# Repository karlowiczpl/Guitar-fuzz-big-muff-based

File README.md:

# Simple guitar fuzz based big muff

The Big Muff is a legendary guitar effects pedal known for its iconic fuzz tone. Its construction typically includes three stages: input buffer, clipping circuit, and output buffer. The input buffer maintains signal integrity, the clipping circuit generates the characteristic distortion, and the output buffer ensures signal strength. Its distinctive sound is cherished by guitarists worldwide

# Schematic

# 3d model

# files

### BRD:
[footprint.brd](footprint.brd)
### STL:
[model.stl](model.stl)
### SCH:
[schematic.sch](schematic.sch)

# Sample photos

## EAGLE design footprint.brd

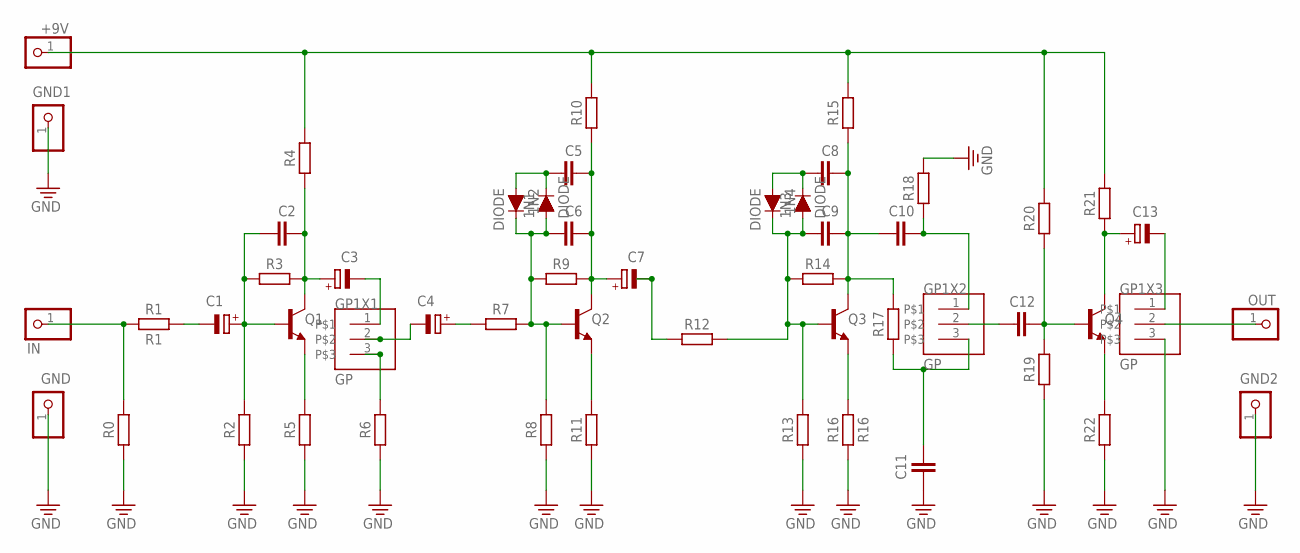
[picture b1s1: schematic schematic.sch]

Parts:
1N1, 1N2, 1N3, 1N4: DIODE; DIODE-1N4148
+9V: PINHD-1X1; 1X01
C1, C3, C4, C7, C13: C; CAP
C2, C5, C6, C8, C9, C10, C11, C12: CUN; CAPPRR250W50L310T100H650B
GND, GND1, GND2: PINHD-1X1; 1X01
GP1X1, GP1X2, GP1X3: GP; HDRV3W64P254_1X3_762X254X838B
IN: PINHD-1X1; 1X01
OUT: PINHD-1X1; 1X01
Q1, Q2, Q3, Q4: BC550B; TO92-EBC
R0, R2, R3, R4, R5, R6, R7, R8, R9, R10, R11, R12, R13, R14, R15, R17, R18, R19, R20, R21, R22: R_AXIAL-7.2MM-PITCH; RESAD724W46L381D178B
R1: R1; RESAD724W46L381D178B
R16: R16; RESAD724W46L381D178B

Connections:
GND: C11.1, GND.1, GND1.1, GND2.1, GP1X3.3, R0.1, R2.1, R5.1, R6.1, R8.1, R11.1, R13.1, R16.1, R18.2, R19.1, R22.1
unnamed: IN.1, R0.2, R1.1
unnamed: C1.2 (-), R1.2
unnamed: C1.1 (+), C2.1, Q1.B, R2.2, R3.1
unnamed: Q1.E, R5.2
unnamed: C2.2, C3.1 (+), Q1.C, R3.2, R4.1
unnamed: C3.2 (-), GP1X1.1
unnamed: C4.2 (-), GP1X1.2
unnamed: GP1X1.3, R6.2
unnamed: C4.1 (+), R7.1
unnamed: 1N1.A, 1N2.C, C6.1, Q2.B, R7.2, R8.2, R9.1
unnamed: C5.2, C6.2, C7.1 (+), Q2.C, R9.2, R10.1
unnamed: 1N1.C, 1N2.A, C5.1
unnamed: Q2.E, R11.2
unnamed: C7.2 (-), R12.1
unnamed: 1N3.A, 1N4.C, C9.1, Q3.B, R12.2, R13.2, R14.1
unnamed: C8.2, C9.2, C10.1, Q3.C, R14.2, R15.1, R17.2
unnamed: 1N3.C, 1N4.A, C8.1
unnamed: Q3.E, R16.2
unnamed: C10.2, GP1X2.1, R18.1
unnamed: C11.2, GP1X2.3, R17.1
unnamed: C12.1, GP1X2.2
unnamed: C12.2, Q4.B, R19.2, R20.1
unnamed: C13.1 (+), Q4.C, R21.1
unnamed: Q4.E, R22.2
unnamed: C13.2 (-), GP1X3.1
unnamed: GP1X3.2, OUT.1
unnamed: +9V.1, R4.2, R10.2, R15.2, R20.2, R21.2

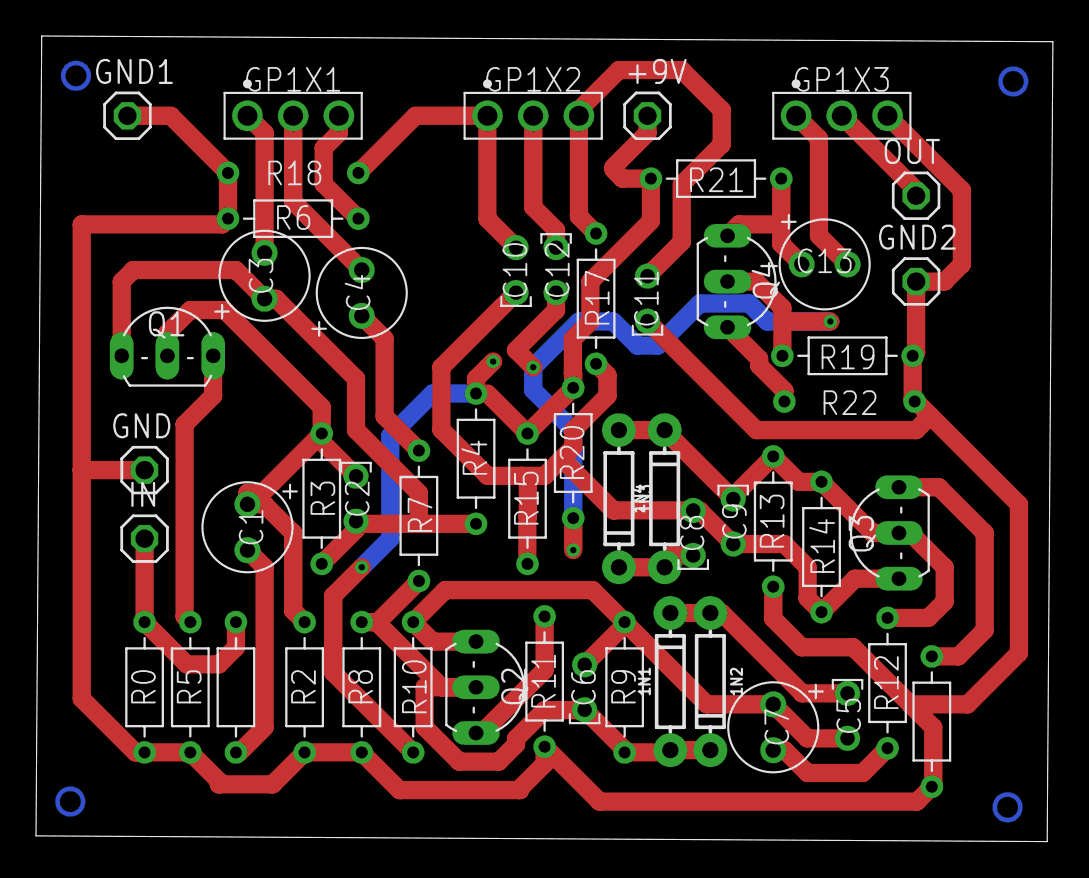
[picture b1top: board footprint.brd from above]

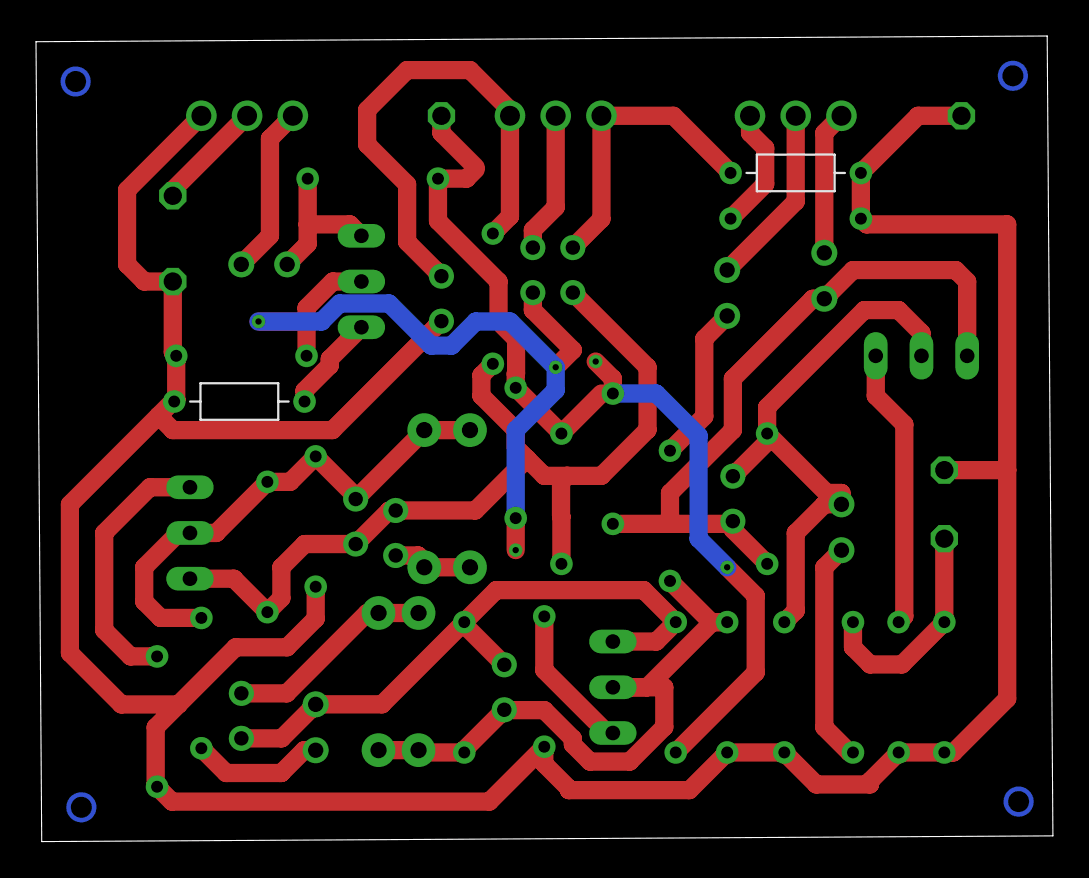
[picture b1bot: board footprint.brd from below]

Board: 2 copper layers, 56.5 x 44.8 mm, 53 parts (2 on the bottom side), 28 nets.
